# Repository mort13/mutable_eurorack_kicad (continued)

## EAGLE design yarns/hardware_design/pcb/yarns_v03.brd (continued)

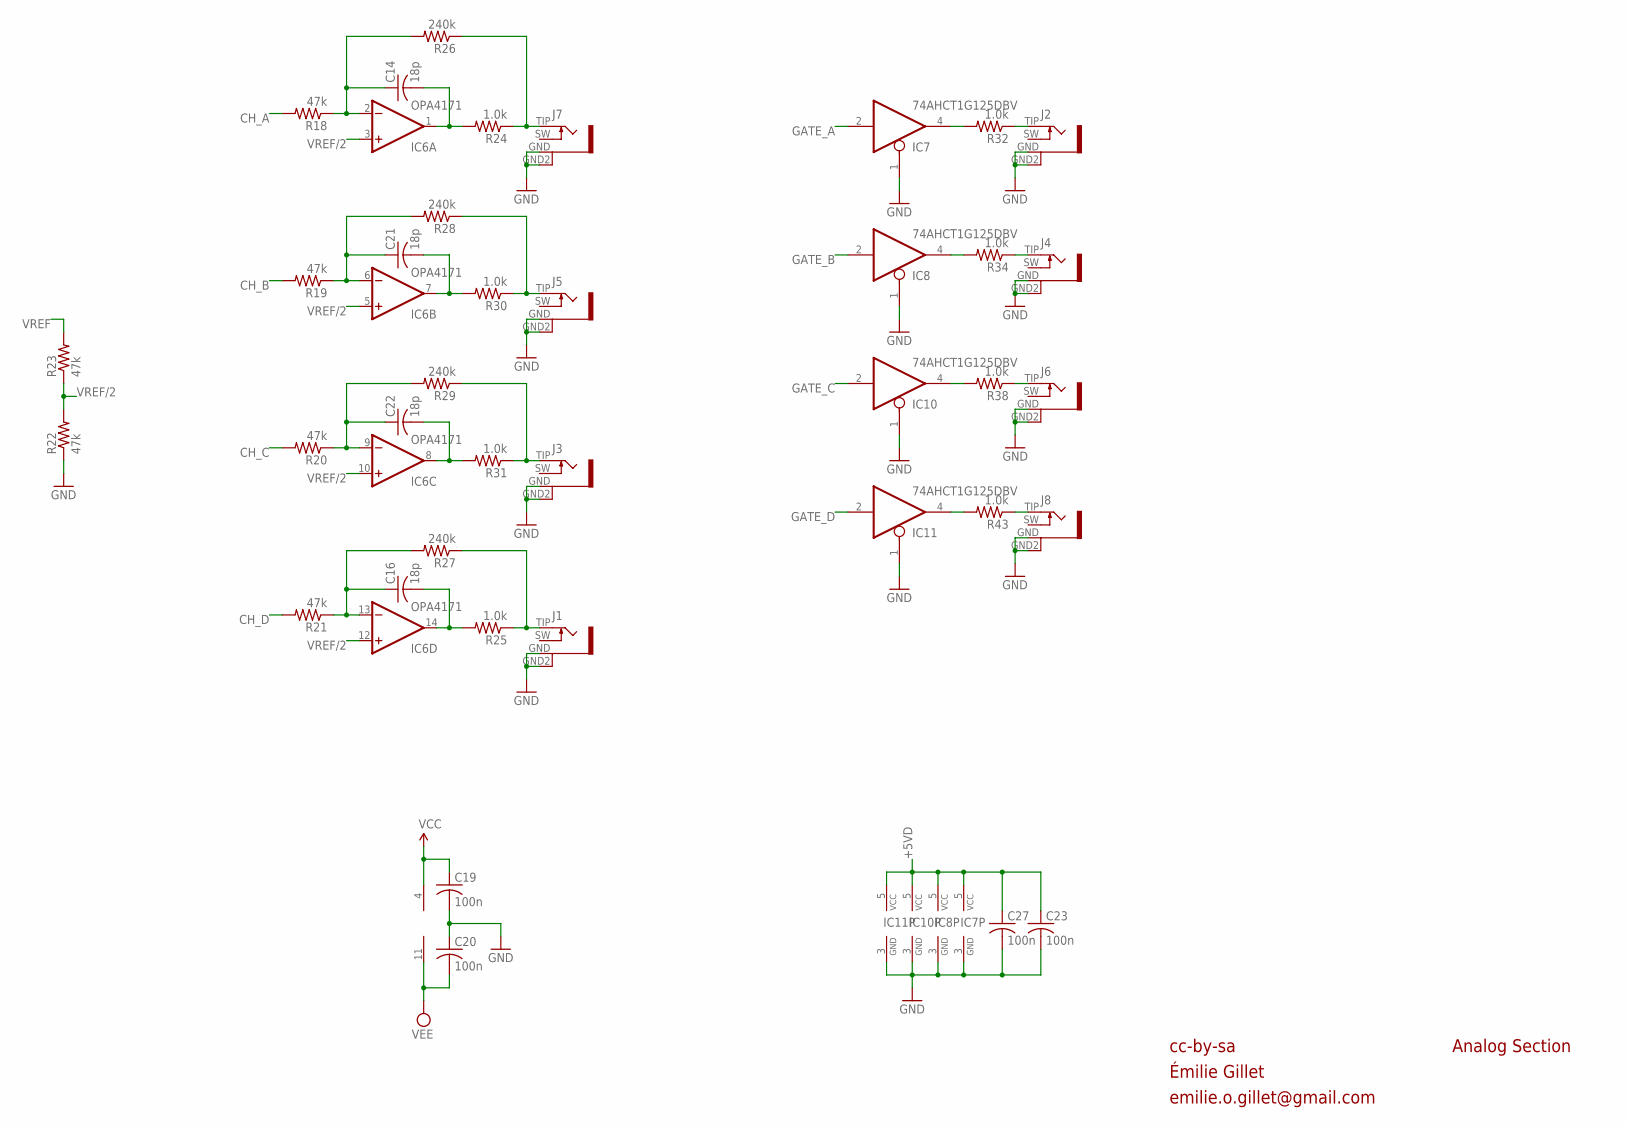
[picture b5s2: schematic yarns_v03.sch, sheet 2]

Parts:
C14, C16, C21, C22: 18p; C0603
C19, C20, C23, C27: 100n; C0603
IC6: OPA4171; SO14
IC7, IC8, IC10, IC11: 74AHCT1G125DBV; SOT23-5
J1, J2, J3, J4, J5, J6, J7, J8: PJ301WQP; WQP_PJ_301BM
R18, R19, R20, R21, R22, R23: 47k; R0603
R24, R25, R30, R31, R32, R34, R38, R43: 1.0k; R0603
R26, R27, R28, R29: 240k; R0603

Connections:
+5VD: C23.1, C27.1, IC7.5 (VCC), IC8.5 (VCC), IC10.5 (VCC), IC11.5 (VCC); also elsewhere on the board
AOUT: J2.TIP (2), R32.1
CH_A: R18.2; also elsewhere on the board
CH_B: R19.2; also elsewhere on the board
CH_C: R20.2; also elsewhere on the board
CH_D: R21.2; also elsewhere on the board
GATE_A: IC7.2 (I); also elsewhere on the board
GATE_B: IC8.2 (I); also elsewhere on the board
GATE_C: IC10.2 (I); also elsewhere on the board
GATE_D: IC11.2 (I); also elsewhere on the board
GND: C19.2, C20.1, C23.2, C27.2, IC7.1 (OE), IC7.3 (GND), IC8.1 (OE), IC8.3 (GND), IC10.1 (OE), IC10.3 (GND), IC11.1 (OE), IC11.3 (GND), J1.GND (1), J1.GND2 (4), J2.GND (1), J2.GND2 (4), J3.GND (1), J3.GND2 (4), J4.GND (1), J4.GND2 (4), J5.GND (1), J5.GND2 (4), J6.GND (1), J6.GND2 (4), J7.GND (1), J7.GND2 (4), J8.GND (1), J8.GND2 (4), R22.1; also elsewhere on the board
unnamed: C22.1, IC6.9 (-IN), R20.1, R29.2
unnamed: IC7.4 (O), R32.2
unnamed: IC8.4 (O), R34.2
unnamed: IC10.4 (O), R38.2
unnamed: IC11.4 (O), R43.2
unnamed: C14.2, IC6.1 (OUT), R24.2
unnamed: J6.TIP (2), R38.1
unnamed: J8.TIP (2), R43.1
unnamed: C21.2, IC6.7 (OUT), R30.2
unnamed: C22.2, IC6.8 (OUT), R31.2
unnamed: C16.2, IC6.14 (OUT), R25.2
unnamed: J7.TIP (2), R24.1, R26.1
unnamed: J3.TIP (2), R29.1, R31.1
unnamed: J4.TIP (2), R34.1
unnamed: J1.TIP (2), R25.1, R27.1
unnamed: C16.1, IC6.13 (-IN), R21.1, R27.2
unnamed: C21.1, IC6.6 (-IN), R19.1, R28.2
unnamed: C14.1, IC6.2 (-IN), R18.1, R26.2
unnamed: J5.TIP (2), R28.1, R30.1
VCC: C19.1, IC6.4 (V+); also elsewhere on the board
VEE: C20.2, IC6.11 (V-); also elsewhere on the board
VREF: R23.2; also elsewhere on the board
VREF/2: IC6.3 (+IN), IC6.5 (+IN), IC6.10 (+IN), IC6.12 (+IN), R22.2, R23.1

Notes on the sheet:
cc-by-sa
Analog Section
Émilie Gillet
emilie.o.gillet@gmail.com

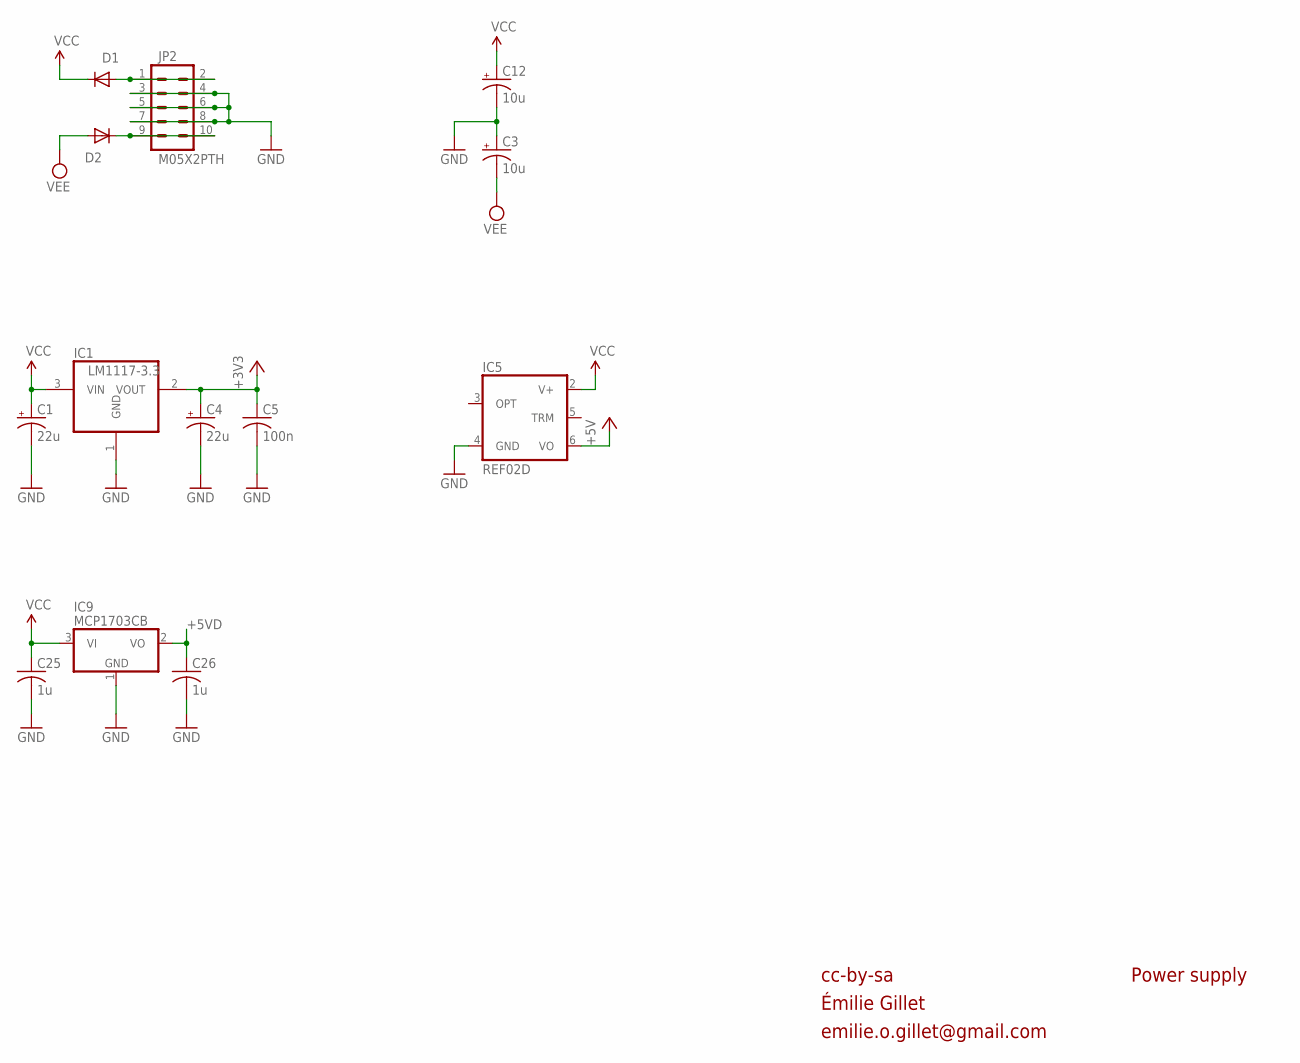
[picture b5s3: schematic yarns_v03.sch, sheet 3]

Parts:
C1, C4: 22u; PANASONIC_C
C3, C12: 10u; PANASONIC_A
C5: 100n; C0603
C25, C26: 1u; C0603
D1, D2: 1N5819HW; SOD123
IC1: LM1117-3.3; SOT223
IC5: REF02D; SO08
IC9: MCP1703CB; SOT23
JP2: M05X2PTH; AVR_ICSP

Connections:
+3V3: C4.+, C5.1, IC1.2 (VOUT); also elsewhere on the board
+5V: IC5.6 (VO); also elsewhere on the board
+5VD: C26.1, IC9.2 (VO); also elsewhere on the board
GND: C1.-, C3.+, C4.-, C5.2, C12.-, C25.2, C26.2, IC1.1 (GND), IC5.4 (GND), IC9.1 (GND), JP2.3, JP2.4, JP2.5, JP2.6, JP2.7, JP2.8; also elsewhere on the board
unnamed: D1.A, JP2.1, JP2.2
unnamed: D2.C, JP2.9, JP2.10
VCC: C1.+, C12.+, C25.1, D1.C, IC1.3 (VIN), IC5.2 (V+), IC9.3 (VI); also elsewhere on the board
VEE: C3.-, D2.A; also elsewhere on the board

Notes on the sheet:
cc-by-sa
Power supply
Émilie Gillet
emilie.o.gillet@gmail.com

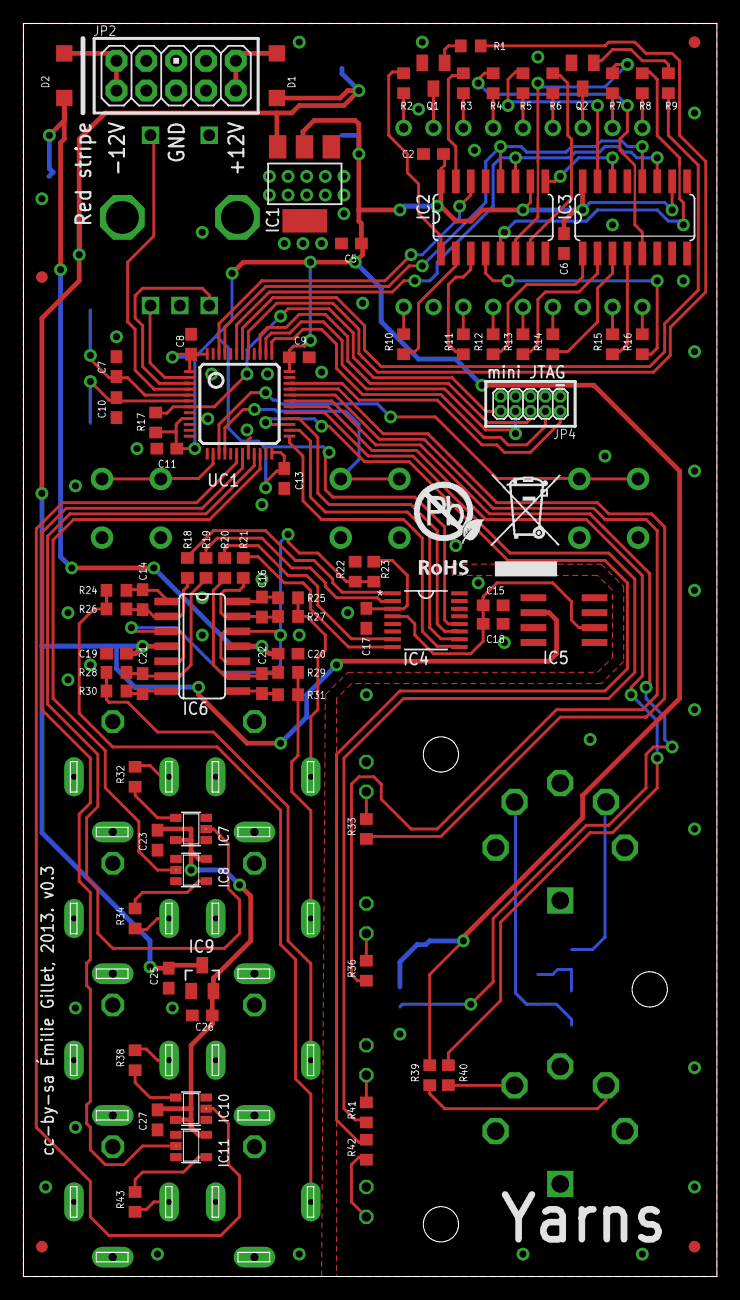
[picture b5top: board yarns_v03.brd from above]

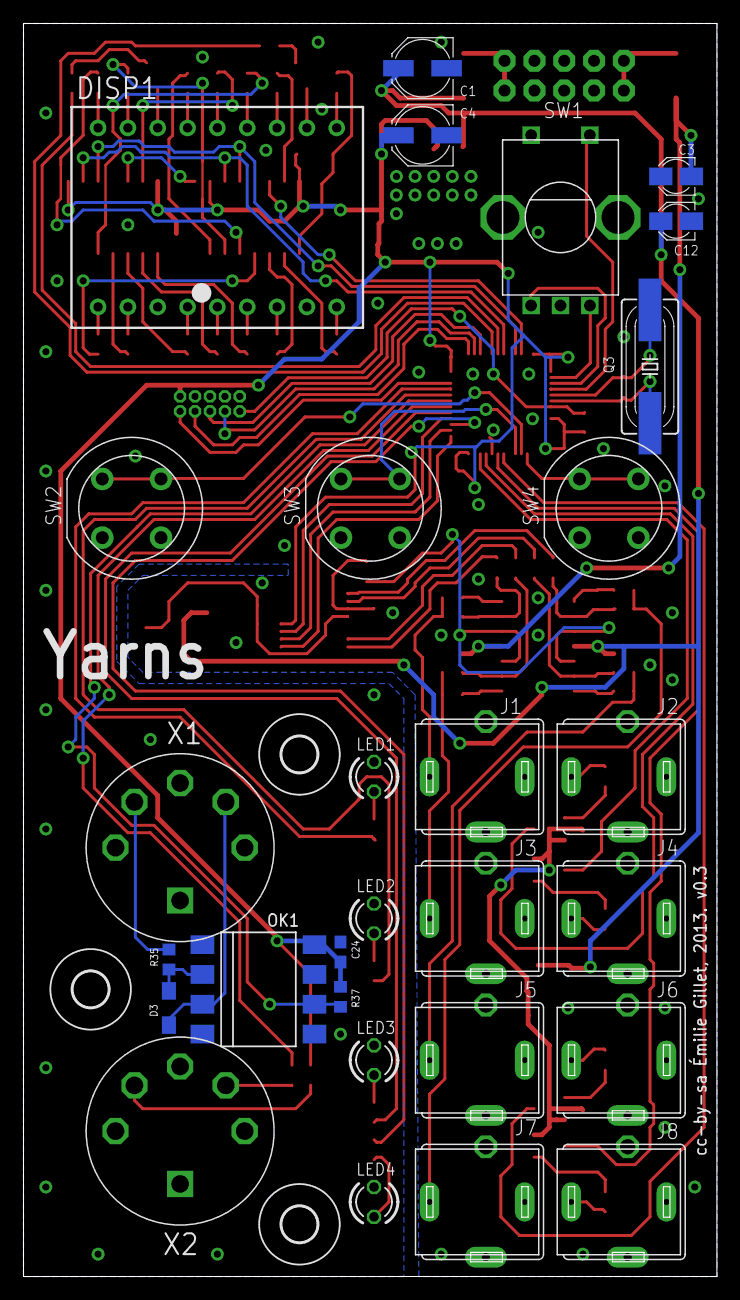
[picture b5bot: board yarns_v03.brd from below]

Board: 2 copper layers, 59.0 x 106.7 mm, 118 parts (32 on the bottom side), 107 nets.

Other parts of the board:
U$2, U$3, U$4: 3,0
U$5: ROHS

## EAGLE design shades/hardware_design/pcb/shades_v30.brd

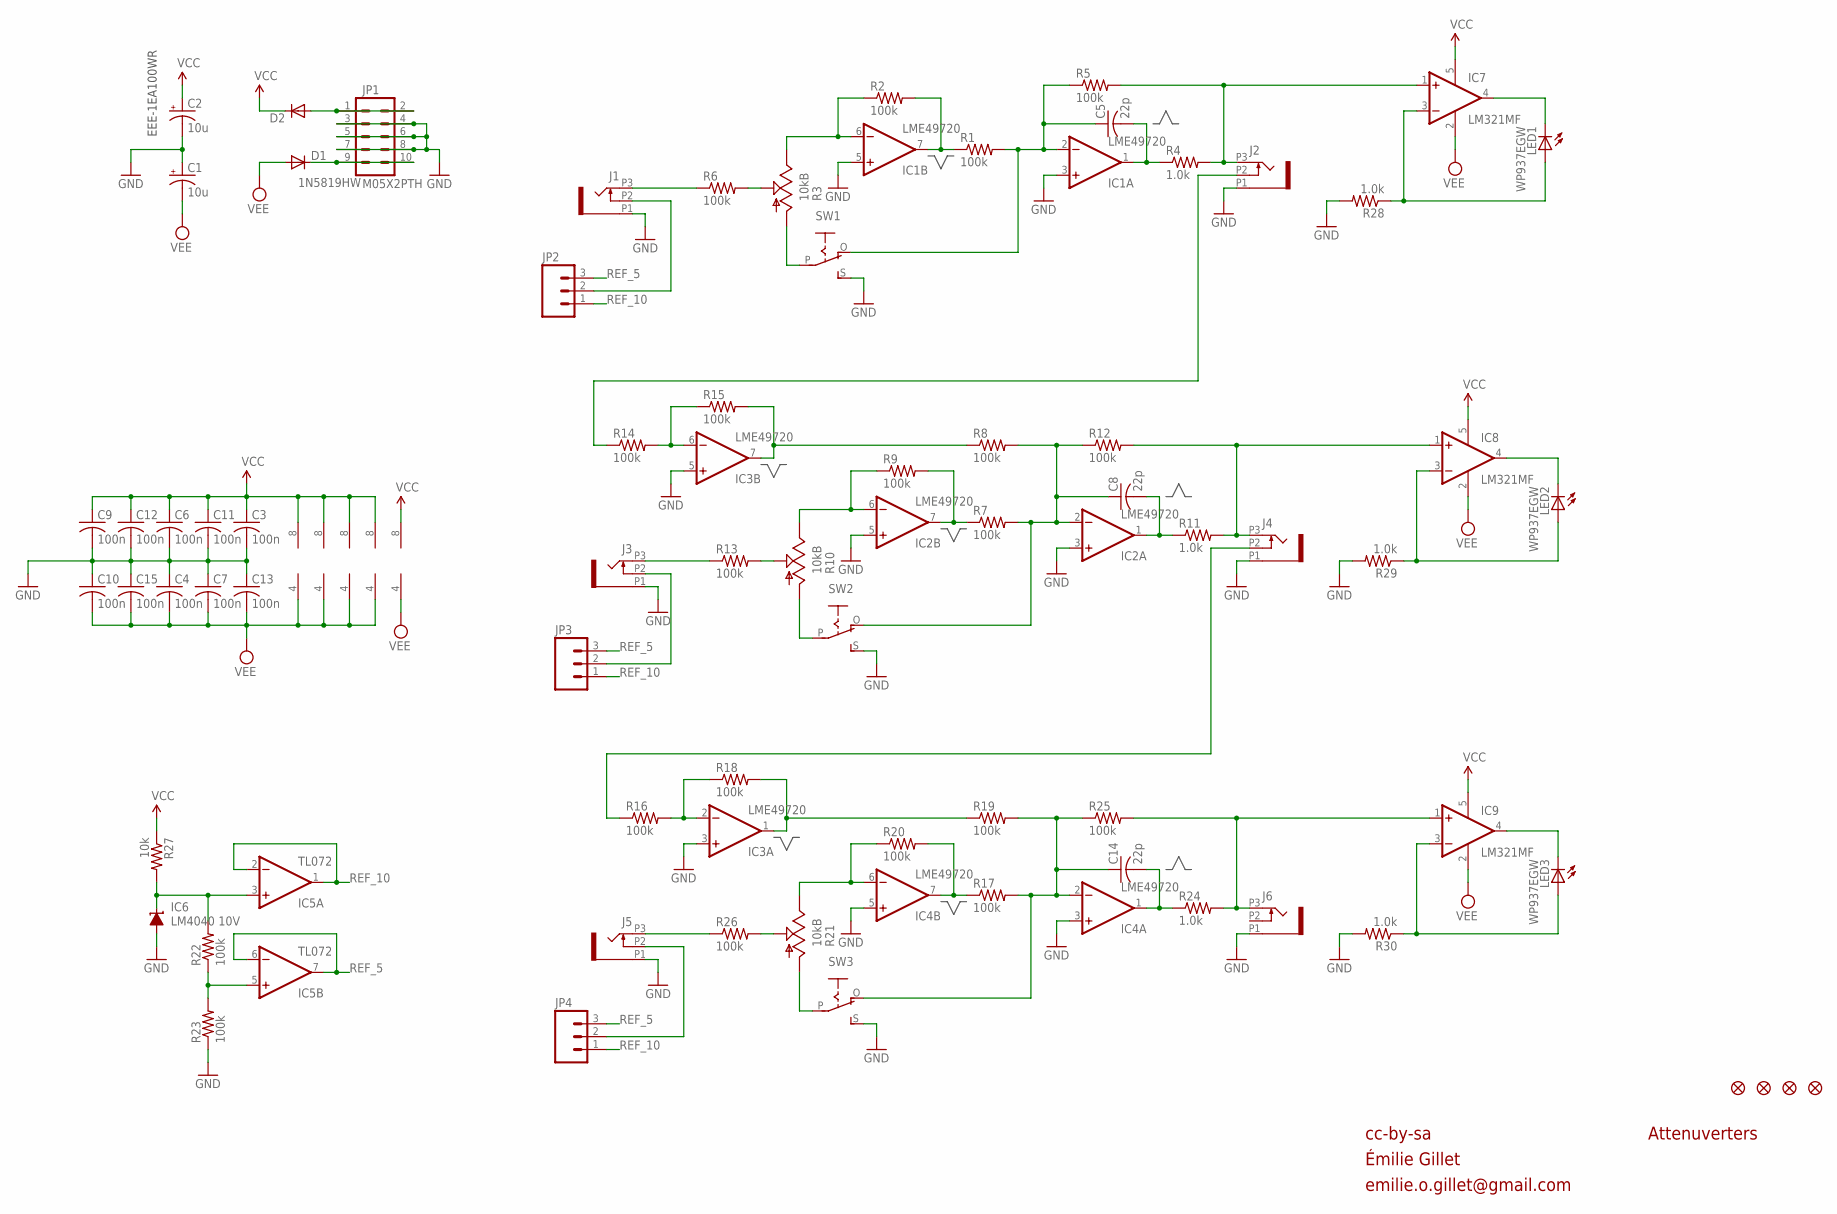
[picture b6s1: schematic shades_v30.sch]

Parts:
C1, C2: 10u; PANASONIC_B
C3, C4, C6, C7, C9, C10, C11, C12, C13, C15: 100n; C0603
C5, C8, C14: 22p; C0603
D1, D2: 1N5819HW; SOD123
F1, F2, F3, F4: FIDUCIAL1X2; FIDUCIAL-1X2
IC1, IC2, IC3, IC4: LME49720; SO08
IC5: TL072; SO08
IC6: LM4040 10V; DBZ_R-PDSO-G3
IC7, IC8, IC9: LM321MF; SOT23-5
J1, J2, J3, J4, J5, J6: PJ301_THONKICONN6; WQP_PJ_301M6
JP1: M05X2PTH; AVR_ICSP
JP2, JP3, JP4: M03PTH; 1X03
LED1, LED2, LED3: WP937EGW; LED3MM
R1, R2, R5, R6, R7, R8, R9, R12, R13, R14, R15, R16, R17, R18, R19, R20, R22, R23, R25, R26: 100k; R0603
R3, R10, R21: 10kB; ALPS_POT_VERTICAL_PS
R4, R11, R24, R28, R29, R30: 1.0k; R0603
R27: 10k; R0603
SW1, SW2, SW3: S-ON-ONSMALL_SLIDE; ES_100SP1T6B11M2QEH_SMALL

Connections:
GND: C1.+, C2.-, C3.2, C4.1, C6.2, C7.1, C9.2, C10.1, C11.2, C12.2, C13.1, C15.1, IC1.3 (+IN), IC1.5 (+IN), IC2.3 (+IN), IC2.5 (+IN), IC3.3 (+IN), IC3.5 (+IN), IC4.3 (+IN), IC4.5 (+IN), IC6.2 (A), J1.P1 (1), J2.P1 (1), J3.P1 (1), J4.P1 (1), J5.P1 (1), J6.P1 (1), JP1.3, JP1.4, JP1.5, JP1.6, JP1.7, JP1.8, R23.1, R28.2, R29.2, R30.2, SW1.S, SW2.S, SW3.S
unnamed: J1.P2 (2), JP2.2
unnamed: J3.P2 (2), JP3.2
unnamed: J5.P2 (2), JP4.2
unnamed: IC7.3 (-IN), LED1.A, R28.1
unnamed: IC5.5 (+IN), R22.1, R23.2
unnamed: D2.A, JP1.1, JP1.2
unnamed: IC7.4 (OUT), LED1.K (C)
unnamed: J1.P3 (3), R6.1
unnamed: R3.P$2 (S), R6.2
unnamed: R3.P$3 (A), SW1.P
unnamed: C5.1, IC1.2 (-IN), R1.2, R5.1, SW1.O
unnamed: IC1.6 (-IN), R2.1, R3.P$1 (E)
unnamed: IC1.7 (OUT), R1.1, R2.2
unnamed: C5.2, IC1.1 (OUT), R4.1
unnamed: J3.P3 (3), R13.1
unnamed: IC8.3 (-IN), LED2.A, R29.1
unnamed: R10.P$2 (S), R13.2
unnamed: R10.P$3 (A), SW2.P
unnamed: D1.C, JP1.9, JP1.10
unnamed: IC2.6 (-IN), R9.1, R10.P$1 (E)
unnamed: IC2.7 (OUT), R7.1, R9.2
unnamed: IC8.4 (OUT), LED2.K (C)
unnamed: C8.2, IC2.1 (OUT), R11.1
unnamed: J5.P3 (3), R26.1
unnamed: R21.P$2 (S), R26.2
unnamed: IC4.6 (-IN), R20.1, R21.P$1 (E)
unnamed: IC4.7 (OUT), R17.1, R20.2
unnamed: C14.2, IC4.1 (OUT), R24.1
unnamed: IC9.3 (-IN), LED3.A, R30.1
unnamed: IC9.4 (OUT), LED3.K (C)
unnamed: IC3.6 (-IN), R14.2, R15.1
unnamed: IC3.2 (-IN), R16.2, R18.1
unnamed: IC3.1 (OUT), R18.2, R19.1
unnamed: IC3.7 (OUT), R8.1, R15.2
unnamed: C14.1, IC4.2 (-IN), R17.2, R19.2, R25.1, SW3.O
unnamed: C8.1, IC2.2 (-IN), R7.2, R8.2, R12.1, SW2.O
OUT_1: IC7.1 (+IN), J2.P3 (3), R4.2, R5.2
OUT_2: IC8.1 (+IN), J4.P3 (3), R11.2, R12.2
OUT_3: IC9.1 (+IN), J6.P3 (3), R24.2, R25.2
REF_5: IC5.6 (-IN), IC5.7 (OUT), JP2.3, JP3.3, JP4.3
REF_10: IC5.1 (OUT), IC5.2 (-IN), JP2.1, JP3.1, JP4.1
REF_10_UNBUF: IC5.3 (+IN), IC6.1 (C), R22.2, R27.2
SEND_1: J2.P2 (2), R14.1
SEND_2: J4.P2 (2), R16.1
SW3: R21.P$3 (A), SW3.P
VCC: C2.+, C3.1, C6.1, C9.1, C11.1, C12.1, D2.C, IC1.8 (V+), IC2.8 (V+), IC3.8 (V+), IC4.8 (V+), IC5.8 (V+), IC7.5 (V+), IC8.5 (V+), IC9.5 (V+), R27.1
VEE: C1.-, C4.2, C7.2, C10.2, C13.2, C15.2, D1.A, IC1.4 (V-), IC2.4 (V-), IC3.4 (V-), IC4.4 (V-), IC5.4 (V-), IC7.2 (V-), IC8.2 (V-), IC9.2 (V-)

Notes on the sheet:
cc-by-sa
Attenuverters
EEE-1EA100WR
Émilie Gillet
emilie.o.gillet@gmail.com

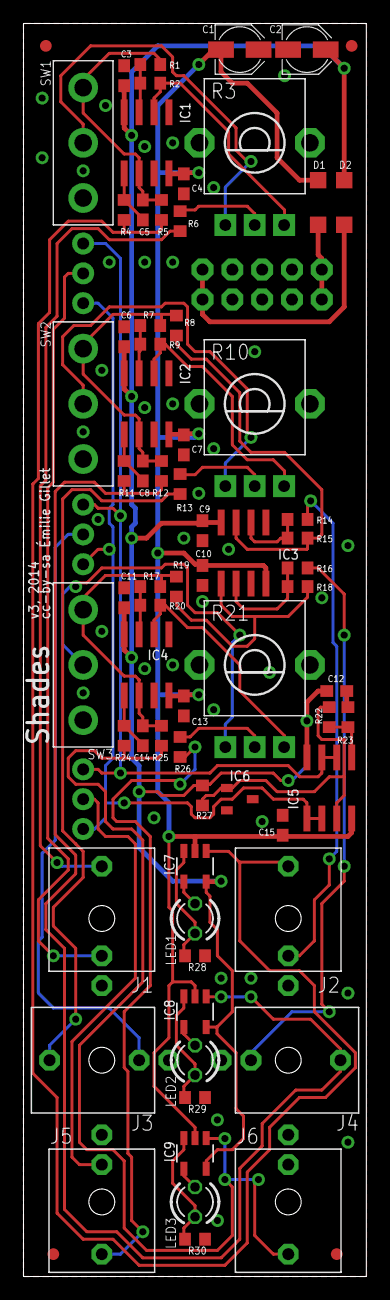
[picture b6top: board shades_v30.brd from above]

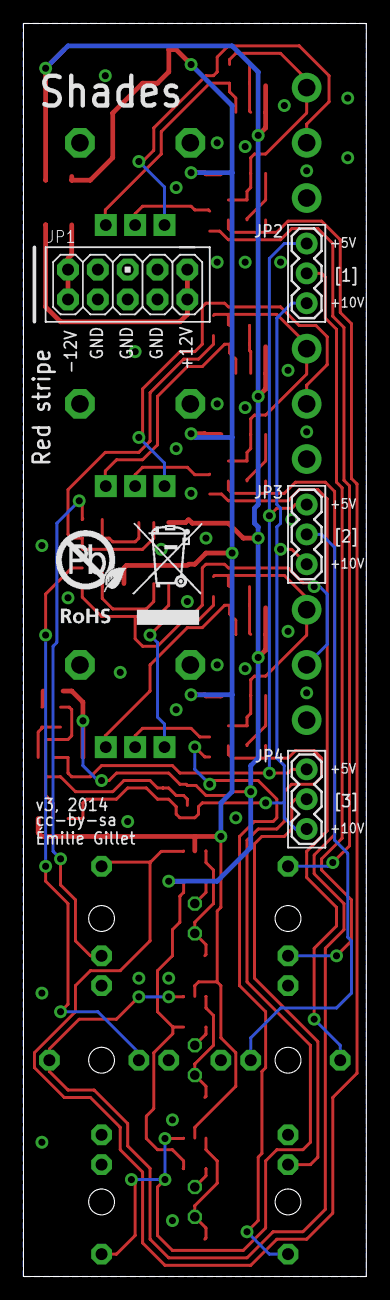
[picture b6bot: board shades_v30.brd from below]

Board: 2 copper layers, 29.2 x 106.7 mm, 77 parts (5 on the bottom side), 48 nets.

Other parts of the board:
U$2: ROHS

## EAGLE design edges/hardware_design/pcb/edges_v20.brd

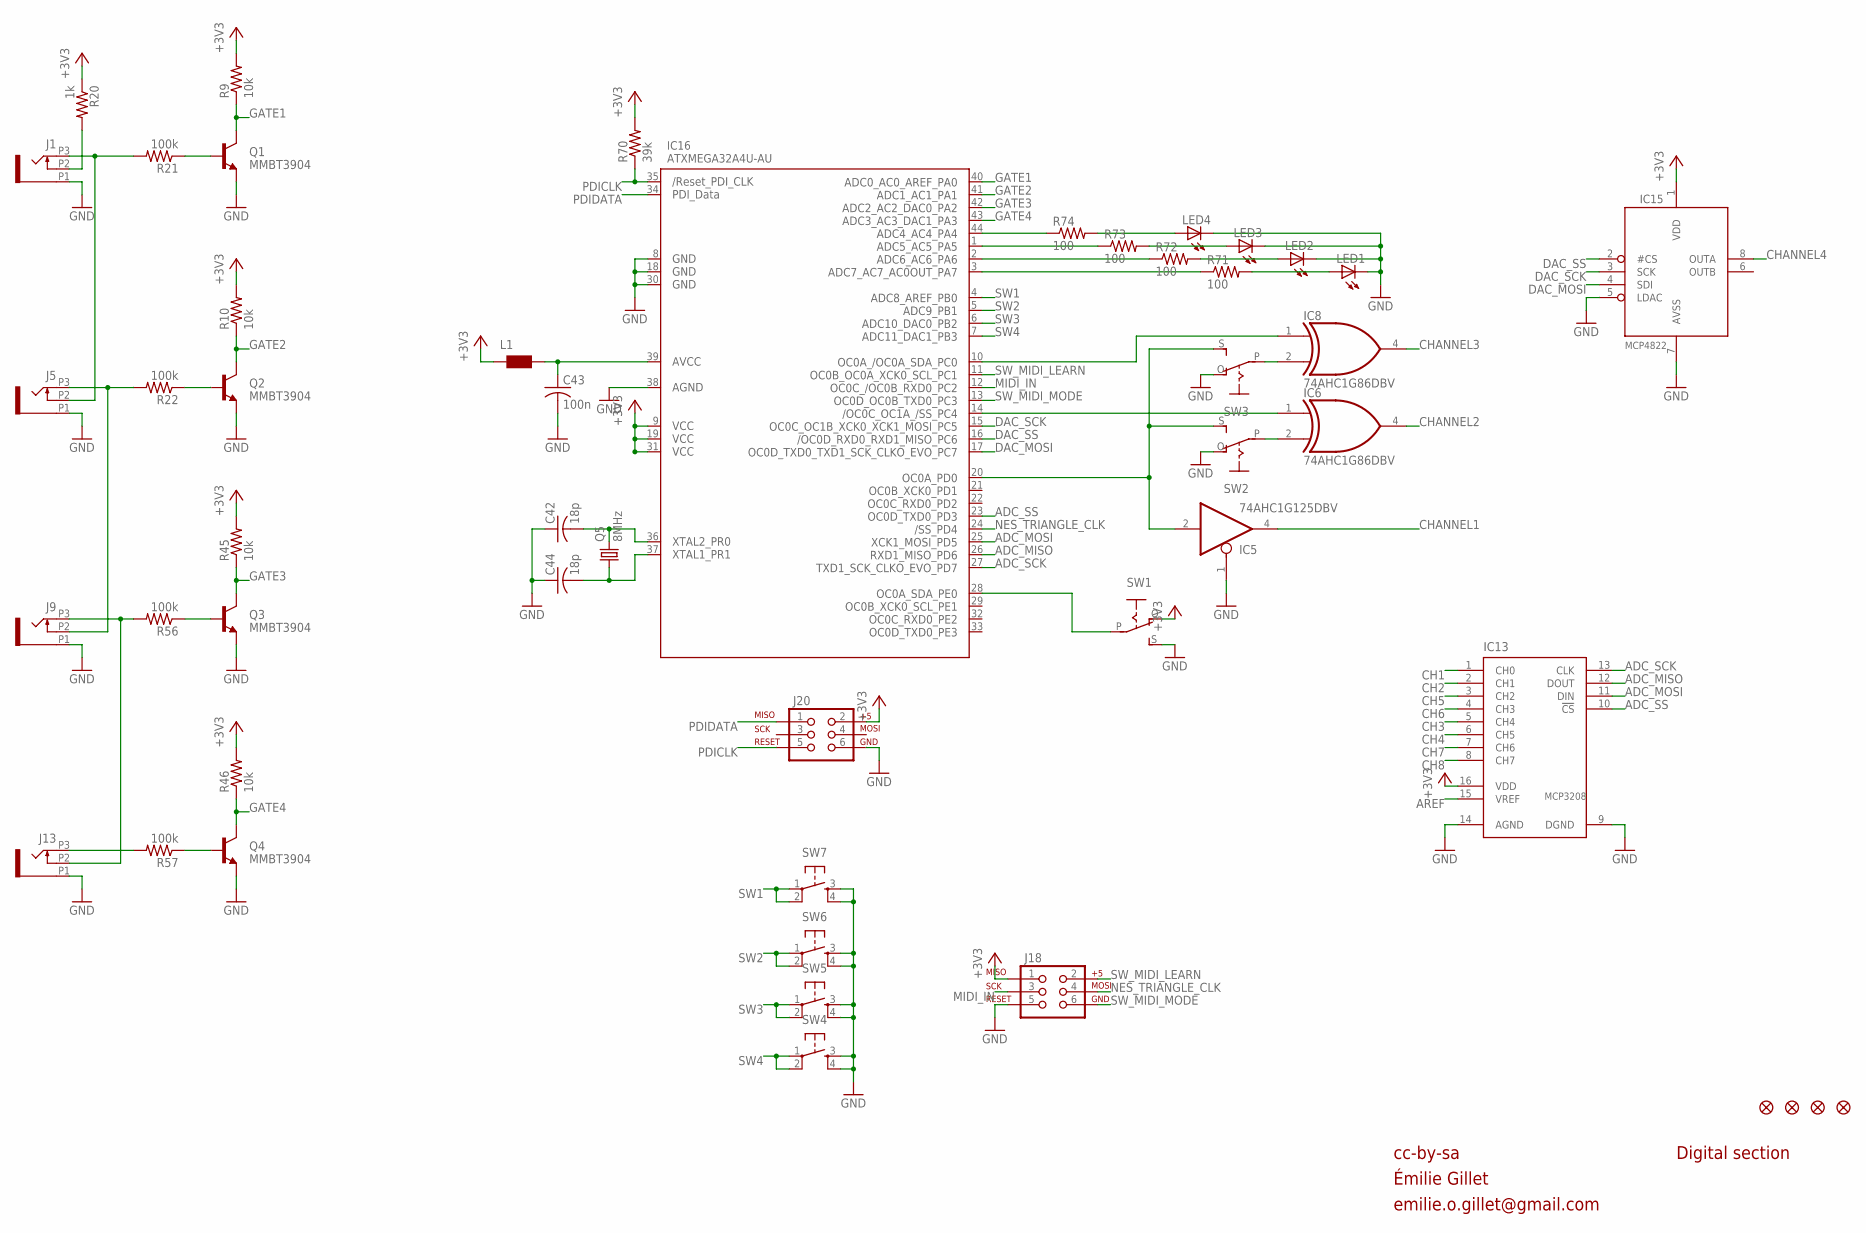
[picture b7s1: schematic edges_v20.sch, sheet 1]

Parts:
C42, C44: 18p; C0603
C43: 100n; C0603
IC5: 74AHC1G125DBV; SOT23-5
IC6, IC8: 74AHC1G86DBV; SOT23-5
IC13: MCP3208; SO16
IC15: MCP4822; SO08
IC16: ATXMEGA32A4U-AU; TQFP44
J1, J5, J9, J13: PJ301_THONKICONN6; WQP_PJ_301M6
J18, J20: AVR_SPI_PRG_6PTH; 2X3
JP1, JP2, JP3, JP4: FIDUCIAL1X2; FIDUCIAL-1X2
L1: WE-CBF_0603; 0603
LED1, LED2, LED3, LED4: LED3MM
Q1, Q2, Q3, Q4: MMBT3904; SOT23-BEC
Q5: 8MHz; HC49U70
R9, R10, R45, R46: 10k; R0603
R20: 1k; R0603
R21, R22, R56, R57: 100k; R0603
R70: 39k; R0603
R71, R72, R73, R74: 100; R0603
SW1, SW2, SW3: S-ON-ONSMALL_SLIDE; ES_100SP1T6B11M2QEH_SMALL
SW4, SW5, SW6, SW7: TAC_SWITCHPTH; TACTILE-PTH

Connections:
+3V3: IC13.16 (VDD), IC15.1 (VDD), IC16.9 (VCC1), IC16.19 (VCC2), IC16.31 (VCC3), J18.1, J20.2, L1.1, R9.2, R10.2, R20.1, R45.2, R46.2, R70.2, SW1.O; also elsewhere on the board
ADC_MISO: IC13.12 (DOUT), IC16.26 (PD6)
ADC_MOSI: IC13.11 (DIN), IC16.25 (PD5)
ADC_SCK: IC13.13 (CLK), IC16.27 (PD7)
ADC_SS: IC13.10 (!CS), IC16.23 (PD3)
AREF: IC13.15 (VREF); also elsewhere on the board
CH1: IC13.1 (CH0); also elsewhere on the board
CH2: IC13.2 (CH1); also elsewhere on the board
CH3: IC13.5 (CH4); also elsewhere on the board
CH4: IC13.6 (CH5); also elsewhere on the board
CH5: IC13.3 (CH2); also elsewhere on the board
CH6: IC13.4 (CH3); also elsewhere on the board
CH7: IC13.7 (CH6); also elsewhere on the board
CH8: IC13.8 (CH7); also elsewhere on the board
CHANNEL1: IC5.4 (O); also elsewhere on the board
CHANNEL2: IC6.4 (O); also elsewhere on the board
CHANNEL3: IC8.4 (O); also elsewhere on the board
CHANNEL4: IC15.8 (OUTA); also elsewhere on the board
DAC_MOSI: IC15.4 (SDI), IC16.17 (PC7)
DAC_SCK: IC15.3 (SCK), IC16.15 (PC5)
DAC_SS: IC15.2 (#CS), IC16.16 (PC6)
GATE1: IC16.40 (PA0), Q1.C, R9.1
GATE1_IN: J1.P3 (3), J5.P2 (2), R21.2
GATE1_LED: LED4.A, R74.2
GATE2: IC16.41 (PA1), Q2.C, R10.1
GATE2_IN: J5.P3 (3), J9.P2 (2), R22.2
GATE2_LED: LED3.A, R73.2
GATE3: IC16.42 (PA2), Q3.C, R45.1
GATE3_IN: J9.P3 (3), J13.P2 (2), R56.2
GATE3_LED: LED2.A, R72.2
GATE4: IC16.43 (PA3), Q4.C, R46.1
GATE4_IN: J13.P3 (3), R57.2
GATE4_LED: LED1.A, R71.2
GND: C42.1, C43.2, C44.1, IC5.1 (OE), IC13.9 (DGND), IC13.14 (AGND), IC15.5 (LDAC), IC15.7 (AVSS), IC16.8 (GND1), IC16.18 (GND2), IC16.30 (GND3), IC16.38 (AGND), J1.P1 (1), J5.P1 (1), J9.P1 (1), J13.P1 (1), J18.5, J20.6, LED1.K (C), LED2.K (C), LED3.K (C), LED4.K (C), Q1.E, Q2.E, Q3.E, Q4.E, SW1.S, SW2.O, SW3.O, SW4.3, SW4.4, SW5.3, SW5.4, SW6.3, SW6.4, SW7.3, SW7.4; also elsewhere on the board
MIDI_IN: IC16.12 (PC2), J18.3
unnamed: Q1.B, R21.1
unnamed: Q2.B, R22.1
unnamed: Q3.B, R56.1
unnamed: IC16.44 (PA4), R74.1
unnamed: IC16.1 (PA5), R73.1
unnamed: IC16.2 (PA6), R72.1
unnamed: IC16.3 (PA7), R71.1
unnamed: J1.P2 (2), R20.2
unnamed: IC6.1 (I0), IC16.14 (PC4)
unnamed: IC8.2 (I1), SW3.P
unnamed: IC6.2 (I1), SW2.P
unnamed: C43.1, IC16.39 (AVCC), L1.2
unnamed: IC8.1 (I0), IC16.10 (PC0)
unnamed: IC5.2 (I), IC16.20 (PD0), SW2.S, SW3.S
unnamed: C44.2, IC16.37 (PR1), Q5.1
unnamed: C42.2, IC16.36 (PR0), Q5.2
unnamed: Q4.B, R57.1
NES_TRIANGLE_CLK: IC16.24 (PD4), J18.4
PDICLK: IC16.35 (RESET), J20.5, R70.1
PDIDATA: IC16.34 (PDI_DATA), J20.1
SW1: IC16.4 (PB0), SW7.1, SW7.2
SW2: IC16.5 (PB1), SW6.1, SW6.2
SW3: IC16.6 (PB2), SW5.1, SW5.2
SW4: IC16.7 (PB3), SW4.1, SW4.2
SW_MIDI_LEARN: IC16.11 (PC1), J18.2
SW_MIDI_MODE: IC16.13 (PC3), J18.6
SYNC_SWITCH: IC16.28 (PE0), SW1.P

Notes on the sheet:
cc-by-sa
Digital section
Émilie Gillet
emilie.o.gillet@gmail.com

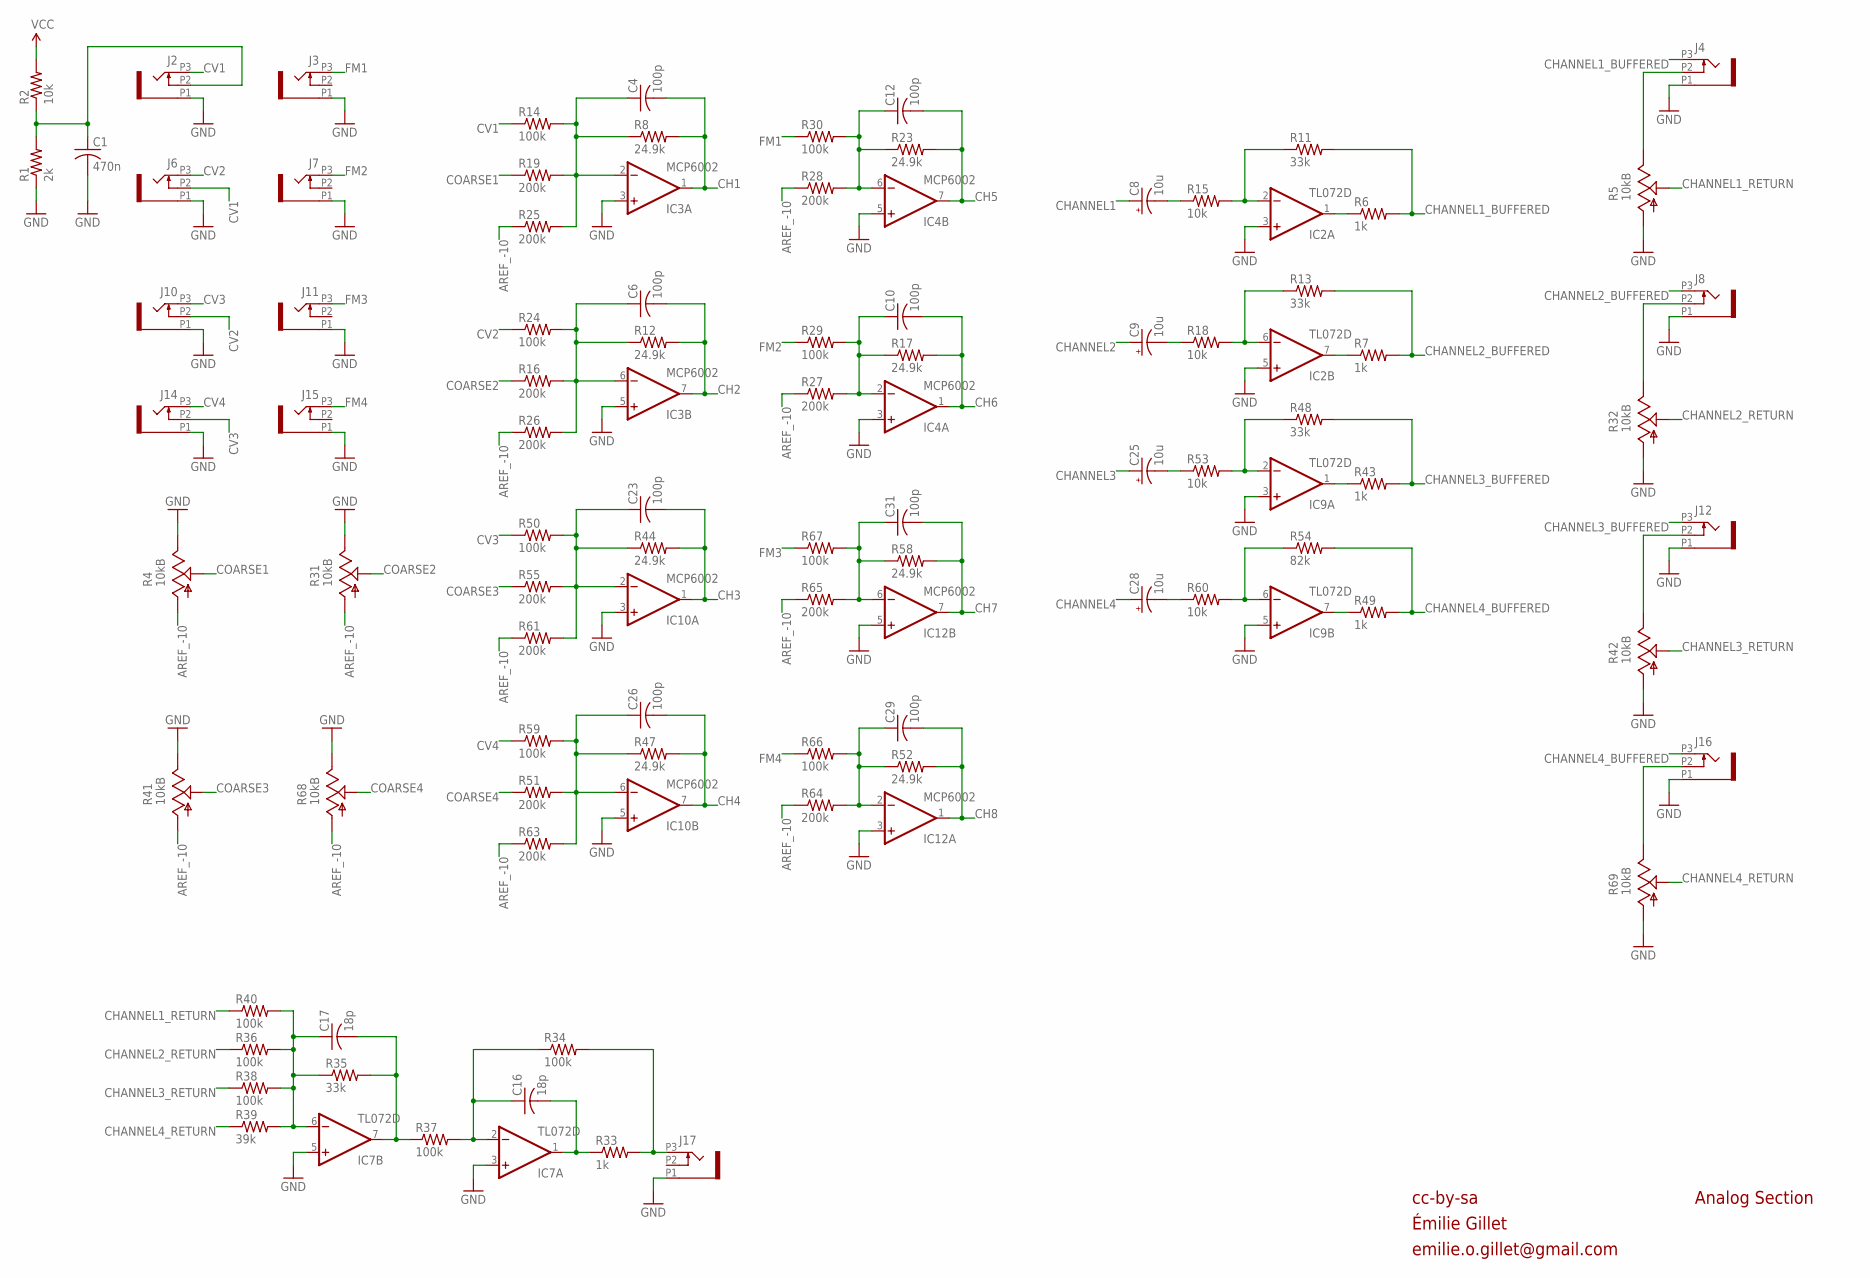
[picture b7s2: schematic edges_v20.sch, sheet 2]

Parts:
C1: 470n; C0603
C4, C6, C10, C12, C23, C26, C29, C31: 100p; C0603
C8, C9, C25, C28: 10u; PANASONIC_B
C16, C17: 18p; C0603
IC2, IC7, IC9: TL072D; SO08
IC3, IC4, IC10, IC12: MCP6002; SO08
J2, J3, J4, J6, J7, J8, J10, J11, J12, J14, J15, J16, J17: PJ301_THONKICONN6; WQP_PJ_301M6
R1: 2k; R0603
R2, R15, R18, R53, R60: 10k; R0603
R4, R5, R31, R32, R41, R42, R68, R69: 10kB; ALPS_POT_VERTICAL_PS
R6, R7, R33, R43, R49: 1k; R0603
R8, R12, R17, R23, R44, R47, R52, R58: 24.9k; R0603
R11, R13, R35, R48: 33k; R0603
R14, R24, R29, R30, R34, R36, R37, R38, R40, R50, R59, R66, R67: 100k; R0603
R16, R19, R25, R26, R27, R28, R51, R55, R61, R63, R64, R65: 200k; R0603
R39: 39k; R0603
R54: 82k; R0603

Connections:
AREF_-10: R4.P$3 (A), R25.1, R26.1, R27.1, R28.1, R31.P$3 (A), R41.P$3 (A), R61.1, R63.1, R64.1, R65.1, R68.P$3 (A); also elsewhere on the board
CH1: C4.2, IC3.1 (OUT), R8.2; also elsewhere on the board
CH2: C6.2, IC3.7 (OUT), R12.2; also elsewhere on the board
CH3: C23.2, IC10.1 (OUT), R44.2; also elsewhere on the board
CH4: C26.2, IC10.7 (OUT), R47.2; also elsewhere on the board
CH5: C12.2, IC4.7 (OUT), R23.2; also elsewhere on the board
CH6: C10.2, IC4.1 (OUT), R17.2; also elsewhere on the board
CH7: C31.2, IC12.7 (OUT), R58.2; also elsewhere on the board
CH8: C29.2, IC12.1 (OUT), R52.2; also elsewhere on the board
CHANNEL1: C8.+; also elsewhere on the board
CHANNEL1_BUFFERED: J4.P3 (3), R6.2, R11.2
CHANNEL1_RETURN: R5.P$2 (S), R40.1
CHANNEL2: C9.+; also elsewhere on the board
CHANNEL2_BUFFERED: J8.P3 (3), R7.2, R13.2
CHANNEL2_RETURN: R32.P$2 (S), R36.1
CHANNEL3: C25.+; also elsewhere on the board
CHANNEL3_BUFFERED: J12.P3 (3), R43.2, R48.2
CHANNEL3_RETURN: R38.1, R42.P$2 (S)
CHANNEL4: C28.+; also elsewhere on the board
CHANNEL4_BUFFERED: J16.P3 (3), R49.2, R54.2
CHANNEL4_RETURN: R39.1, R69.P$2 (S)
COARSE1: R4.P$2 (S), R19.1
COARSE2: R16.1, R31.P$2 (S)
COARSE3: R41.P$2 (S), R55.1
COARSE4: R51.1, R68.P$2 (S)
CV1: J2.P3 (3), J6.P2 (2), R14.1
CV2: J6.P3 (3), J10.P2 (2), R24.1
CV3: J10.P3 (3), J14.P2 (2), R50.1
CV4: J14.P3 (3), R59.1
FM1: J3.P3 (3), R30.1
FM2: J7.P3 (3), R29.1
FM3: J11.P3 (3), R67.1
FM4: J15.P3 (3), R66.1
GND: C1.2, IC2.3 (+IN), IC2.5 (+IN), IC3.3 (+IN), IC3.5 (+IN), IC4.3 (+IN), IC4.5 (+IN), IC7.3 (+IN), IC7.5 (+IN), IC9.3 (+IN), IC9.5 (+IN), IC10.3 (+IN), IC10.5 (+IN), IC12.3 (+IN), IC12.5 (+IN), J2.P1 (1), J3.P1 (1), J4.P1 (1), J6.P1 (1), J7.P1 (1), J8.P1 (1), J10.P1 (1), J11.P1 (1), J12.P1 (1), J14.P1 (1), J15.P1 (1), J16.P1 (1), J17.P1 (1), R1.1, R4.P$1 (E), R5.P$3 (A), R31.P$1 (E), R32.P$3 (A), R41.P$1 (E), R42.P$3 (A), R68.P$1 (E), R69.P$3 (A); also elsewhere on the board
MIX: J17.P3 (3), R33.2, R34.2
unnamed: J8.P2 (2), R32.P$1 (E)
unnamed: C23.1, IC10.2 (-IN), R44.1, R50.2, R55.2, R61.2
unnamed: C10.1, IC4.2 (-IN), R17.1, R27.2, R29.2
unnamed: C26.1, IC10.6 (-IN), R47.1, R51.2, R59.2, R63.2
unnamed: C31.1, IC12.6 (-IN), R58.1, R65.2, R67.2
unnamed: C29.1, IC12.2 (-IN), R52.1, R64.2, R66.2
unnamed: C8.-, R15.1
unnamed: IC2.2 (-IN), R11.1, R15.2
unnamed: IC2.1 (OUT), R6.1
unnamed: C9.-, R18.1
unnamed: IC2.6 (-IN), R13.1, R18.2
unnamed: IC2.7 (OUT), R7.1
unnamed: C25.-, R53.1
unnamed: C12.1, IC4.6 (-IN), R23.1, R28.2, R30.2
unnamed: IC9.2 (-IN), R48.1, R53.2
unnamed: IC9.1 (OUT), R43.1
unnamed: C28.-, R60.1
unnamed: IC9.6 (-IN), R54.1, R60.2
unnamed: IC9.7 (OUT), R49.1
unnamed: C17.1, IC7.6 (-IN), R35.1, R36.2, R38.2, R39.2, R40.2
unnamed: C16.1, IC7.2 (-IN), R34.1, R37.2
unnamed: C16.2, IC7.1 (OUT), R33.1
unnamed: J4.P2 (2), R5.P$1 (E)
unnamed: C17.2, IC7.7 (OUT), R35.2, R37.1
unnamed: J12.P2 (2), R42.P$1 (E)
unnamed: J16.P2 (2), R69.P$1 (E)
unnamed: C6.1, IC3.6 (-IN), R12.1, R16.2, R24.2, R26.2
unnamed: C1.1, J2.P2 (2), R1.2, R2.1
unnamed: C4.1, IC3.2 (-IN), R8.1, R14.2, R19.2, R25.2
VCC: R2.2; also elsewhere on the board

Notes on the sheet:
cc-by-sa
Analog Section
Émilie Gillet
emilie.o.gillet@gmail.com
